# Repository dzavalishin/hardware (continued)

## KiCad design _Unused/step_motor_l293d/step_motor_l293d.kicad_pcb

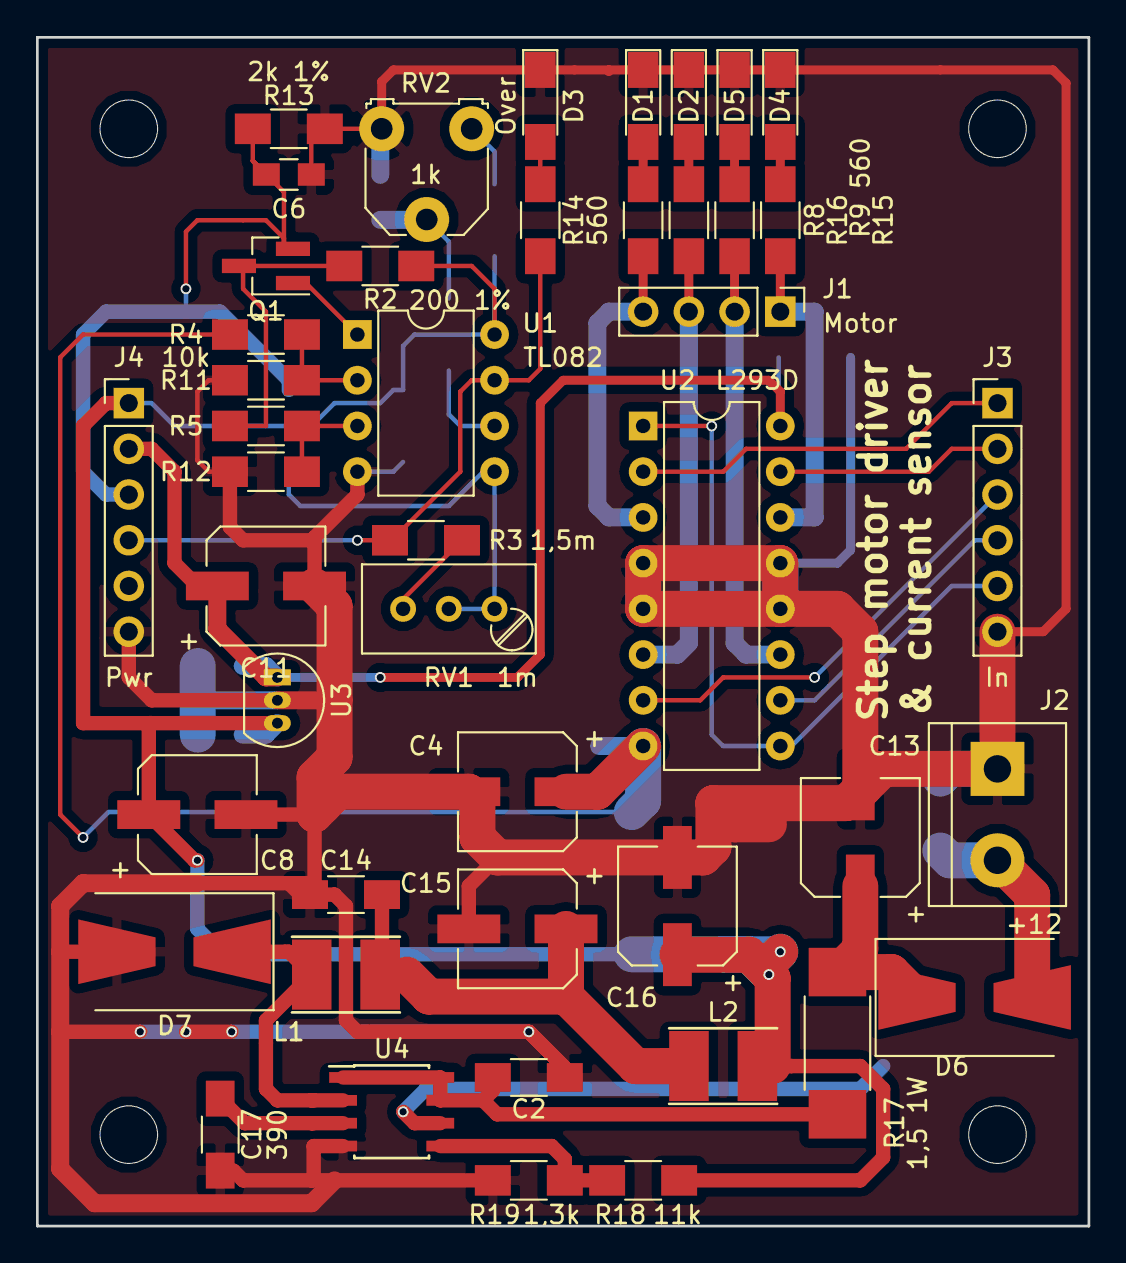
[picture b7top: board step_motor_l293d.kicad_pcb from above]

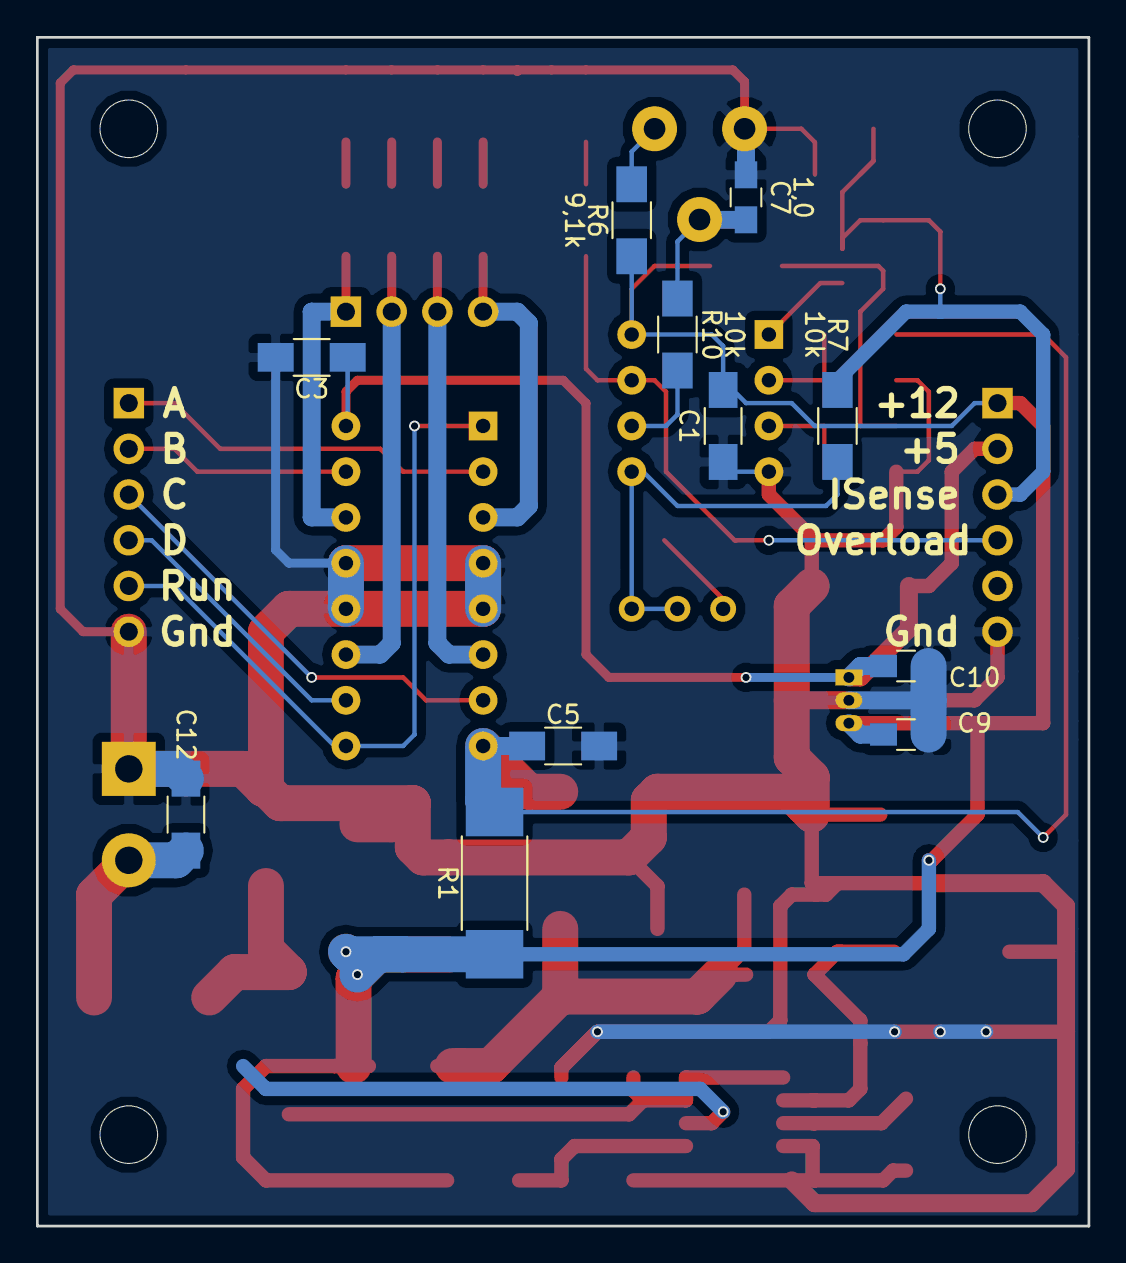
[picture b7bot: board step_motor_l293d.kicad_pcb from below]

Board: 2 copper layers, 58.4 x 66.0 mm, 60 parts (11 on the bottom side), 36 nets.

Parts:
C1, C2, C3, C5, C12, C14: 0,1; C_1206_HandSoldering
C4, C8: 47,0; CP_Elec_6.3x5.3
C6, C7: 1,0; C_0805_HandSoldering
C9, C10: 0,33; C_0805_HandSoldering
C11, C13, C16: 100,0; CP_Elec_6.3x5.7
C15: 220,0; CP_Elec_6.3x5.7
C17: 390; C_1206_HandSoldering
D1: A; LED_1206_HandSoldering
D2: B; LED_1206_HandSoldering
D3: Over; LED_1206_HandSoldering
D4: D; LED_1206_HandSoldering
D5: C; LED_1206_HandSoldering
D6, D7: SS34; D_SMB-SMC_Universal_Handsoldering
Hole: MountingHole_3.2mm_M3
Hole#2, Hole#3, Hole#4: MountingHole_3.2mm_M3
J1: Motor; Pin_Header_Straight_1x04_Pitch2.54mm
J2: +12; TerminalBlock_bornier-2_P5.08mm
J3: In; Pin_Header_Straight_1x06_Pitch2.54mm
J4: Pwr; Pin_Header_Straight_1x06_Pitch2.54mm
L1: 100uH; Inductor_Taiyo-Yuden_NR-40xx_HandSoldering
L2: 47uH; Inductor_Taiyo-Yuden_NR-40xx_HandSoldering
Q1: MMBT3904; SOT-23_Handsoldering
R1: 0,2 2W 1%; R_2512_HandSoldering
R2: 200 1%; R_1206_HandSoldering
R3: 1,5m; R_1206_HandSoldering
R4, R5, R7, R10, R11, R12: 10k; R_1206_HandSoldering
R6: 9,1k; R_1206_HandSoldering
R8, R9, R14, R15, R16: 560; R_1206_HandSoldering
R13: 2k 1%; R_1206_HandSoldering
R17: 1,5 1W; R_2512_HandSoldering
R18: 11k; R_1206_HandSoldering
R19: 1,3k; R_1206_HandSoldering
RV1: 1m; Potentiometer_Trimmer_Bourns_3296W
RV2: 1k; Potentiometer_Triwood_RM-065
U1: TL082; DIP-8_W7.62mm
U2: L293D; DIP-16_W7.62mm
U3: L78L05; TO-92_Inline_Narrow_Oval
U4: MC34063; SOIC-8_3.9x4.9mm_Pitch1.27mm

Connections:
+5V: C3.1, C10.1, C11.1, J4.2, U2.16, U3.1
+12V: C1.1, C8.1, C9.1, C16.1, J4.1, L2.2, R1.1, R2.1, R6.2, R18.2, U1.8, U3.3
/Buck/Power_In: C12.2, D6.2, J2.2
/MA: J3.1, U2.2
/MB: J3.3, U2.7
/MC: J3.4, U2.10
/MD: J3.2, U2.15
/MPower: C4.1, C5.1, R1.2, R4.1, U2.8
/Overload: J4.4, R3.1, R14.2, U1.7
/Run: J3.5, U2.1, U2.9
/Sense: C6.1, J4.3, Q1.2, R7.2, R13.1
GND: C1.2, C2.1, C3.2, C4.2, C5.2, C6.2, C7.2, C8.2, C9.2, C10.2, C11.2, C12.1, C13.2, C14.2, C15.2, C16.2, C17.2, D1.1, D2.1, D3.1, D4.1, D5.1, D7.2, J2.1, J3.6, J4.6, R11.2, R12.2, R13.2, R19.2, RV2.3, U1.4, U2.4, U2.5, U2.12, U2.13, U3.2, U4.4
unnamed: C2.2, R17.2, U4.1, U4.7, U4.8
unnamed: C7.1, R10.2, RV2.2
unnamed: C13.1, D6.1, R17.1, U4.6
unnamed: C14.1, C15.1, L1.2, L2.1
unnamed: C17.1, U4.3
unnamed: D1.2, R8.1
unnamed: D2.2, R9.1
unnamed: D3.2, R14.1
unnamed: D4.2, R15.2
unnamed: D5.2, R16.2
unnamed: D7.1, L1.1, U4.2
unnamed: J1.1, R15.1, U2.14
unnamed: J1.2, R16.1, U2.11
unnamed: J1.3, R9.2, U2.6
unnamed: J1.4, R8.2, U2.3
unnamed: Q1.1, U1.1
unnamed: Q1.3, R2.2, R5.1
unnamed: R3.2, RV1.3
unnamed: R6.1, RV2.1
unnamed: R7.1, RV1.1, RV1.2, U1.5
unnamed: R10.1, U1.6
unnamed: R4.2, R11.1, U1.2
unnamed: R5.2, R12.1, U1.3
unnamed: R18.1, R19.1, U4.5
